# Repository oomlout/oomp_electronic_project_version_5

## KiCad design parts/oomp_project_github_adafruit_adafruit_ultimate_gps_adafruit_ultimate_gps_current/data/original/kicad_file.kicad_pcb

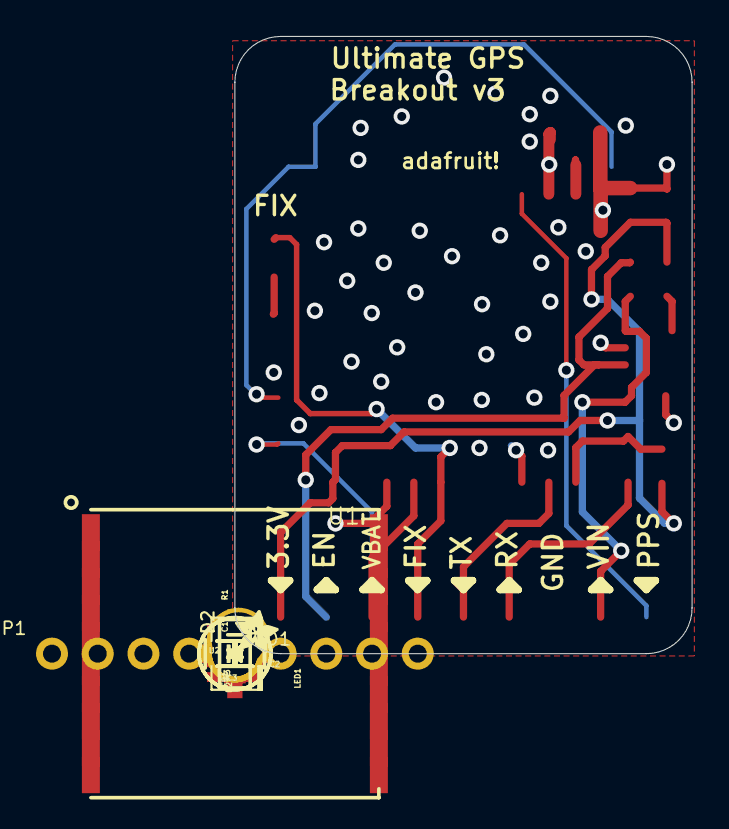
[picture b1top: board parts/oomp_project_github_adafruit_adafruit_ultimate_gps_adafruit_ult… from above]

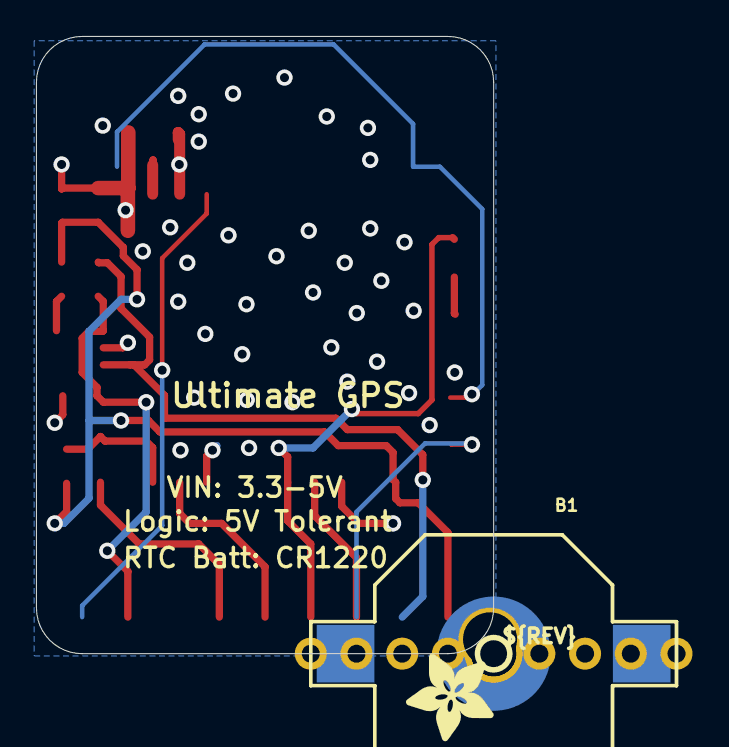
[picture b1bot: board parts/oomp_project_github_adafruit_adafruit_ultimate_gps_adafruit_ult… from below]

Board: 2 copper layers, 25.4 x 34.3 mm, 22 parts (3 on the bottom side), 14 nets.

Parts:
B1: CR1220
C1: 0.1uF; 0805-NO
C2, C3: 10uF; 0805-NO
D1: 1N4148; SOD-323
D2: CUS520; SOD-323
FB1: Ferrite; 0805-NO
FID1, FID2: FIDUCIAL""; FIDUCIAL_1MM
JP1: 1X09_ROUND_70
LED1: RED; CHIPLED_0805
R1: 1K; 0805-NO
R2, R3: 10K; 0805-NO
U1: FGPMMOPA6H
U2: MIC5225-3.3; SOT23-5
U$8, U$9: MOUNTINGHOLE2.5; MOUNTINGHOLE_2.5_PLATED
U$15: ADAFRUIT_2.5MM
U$16: PCBFEAT-REV-040
U$18: ADAFRUIT_5MM
U$20: U.FL

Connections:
1PPS: JP1.1, U1.P$13
3.3V: C1.1, C2.1, FB1.2, JP1.9, R3.1, U1.P$1
ENABLE: JP1.8, R2.1, U2.3
FIX: JP1.6, LED1.A, U1.P$5
GND: B1.-, C1.2, C2.2, C3.2, JP1.3, R1.1, U1.P$3, U1.P$8, U1.P$12, U1.P$19, U2.2, U$20.P$1, U$20.P$2
unnamed: B1.+$1, B1.+$2, D2.A
unnamed: LED1.C, R1.2
unnamed: FB1.1, U2.5
unnamed: U1.P$11, U$20.P$3
RX: D1.C, JP1.4
RX_3V: D1.A, R3.2, U1.P$10
TX: JP1.5, U1.P$9
VBACKUP: D2.C, JP1.7, U1.P$4
VIN: C3.1, JP1.2, R2.2, U2.1

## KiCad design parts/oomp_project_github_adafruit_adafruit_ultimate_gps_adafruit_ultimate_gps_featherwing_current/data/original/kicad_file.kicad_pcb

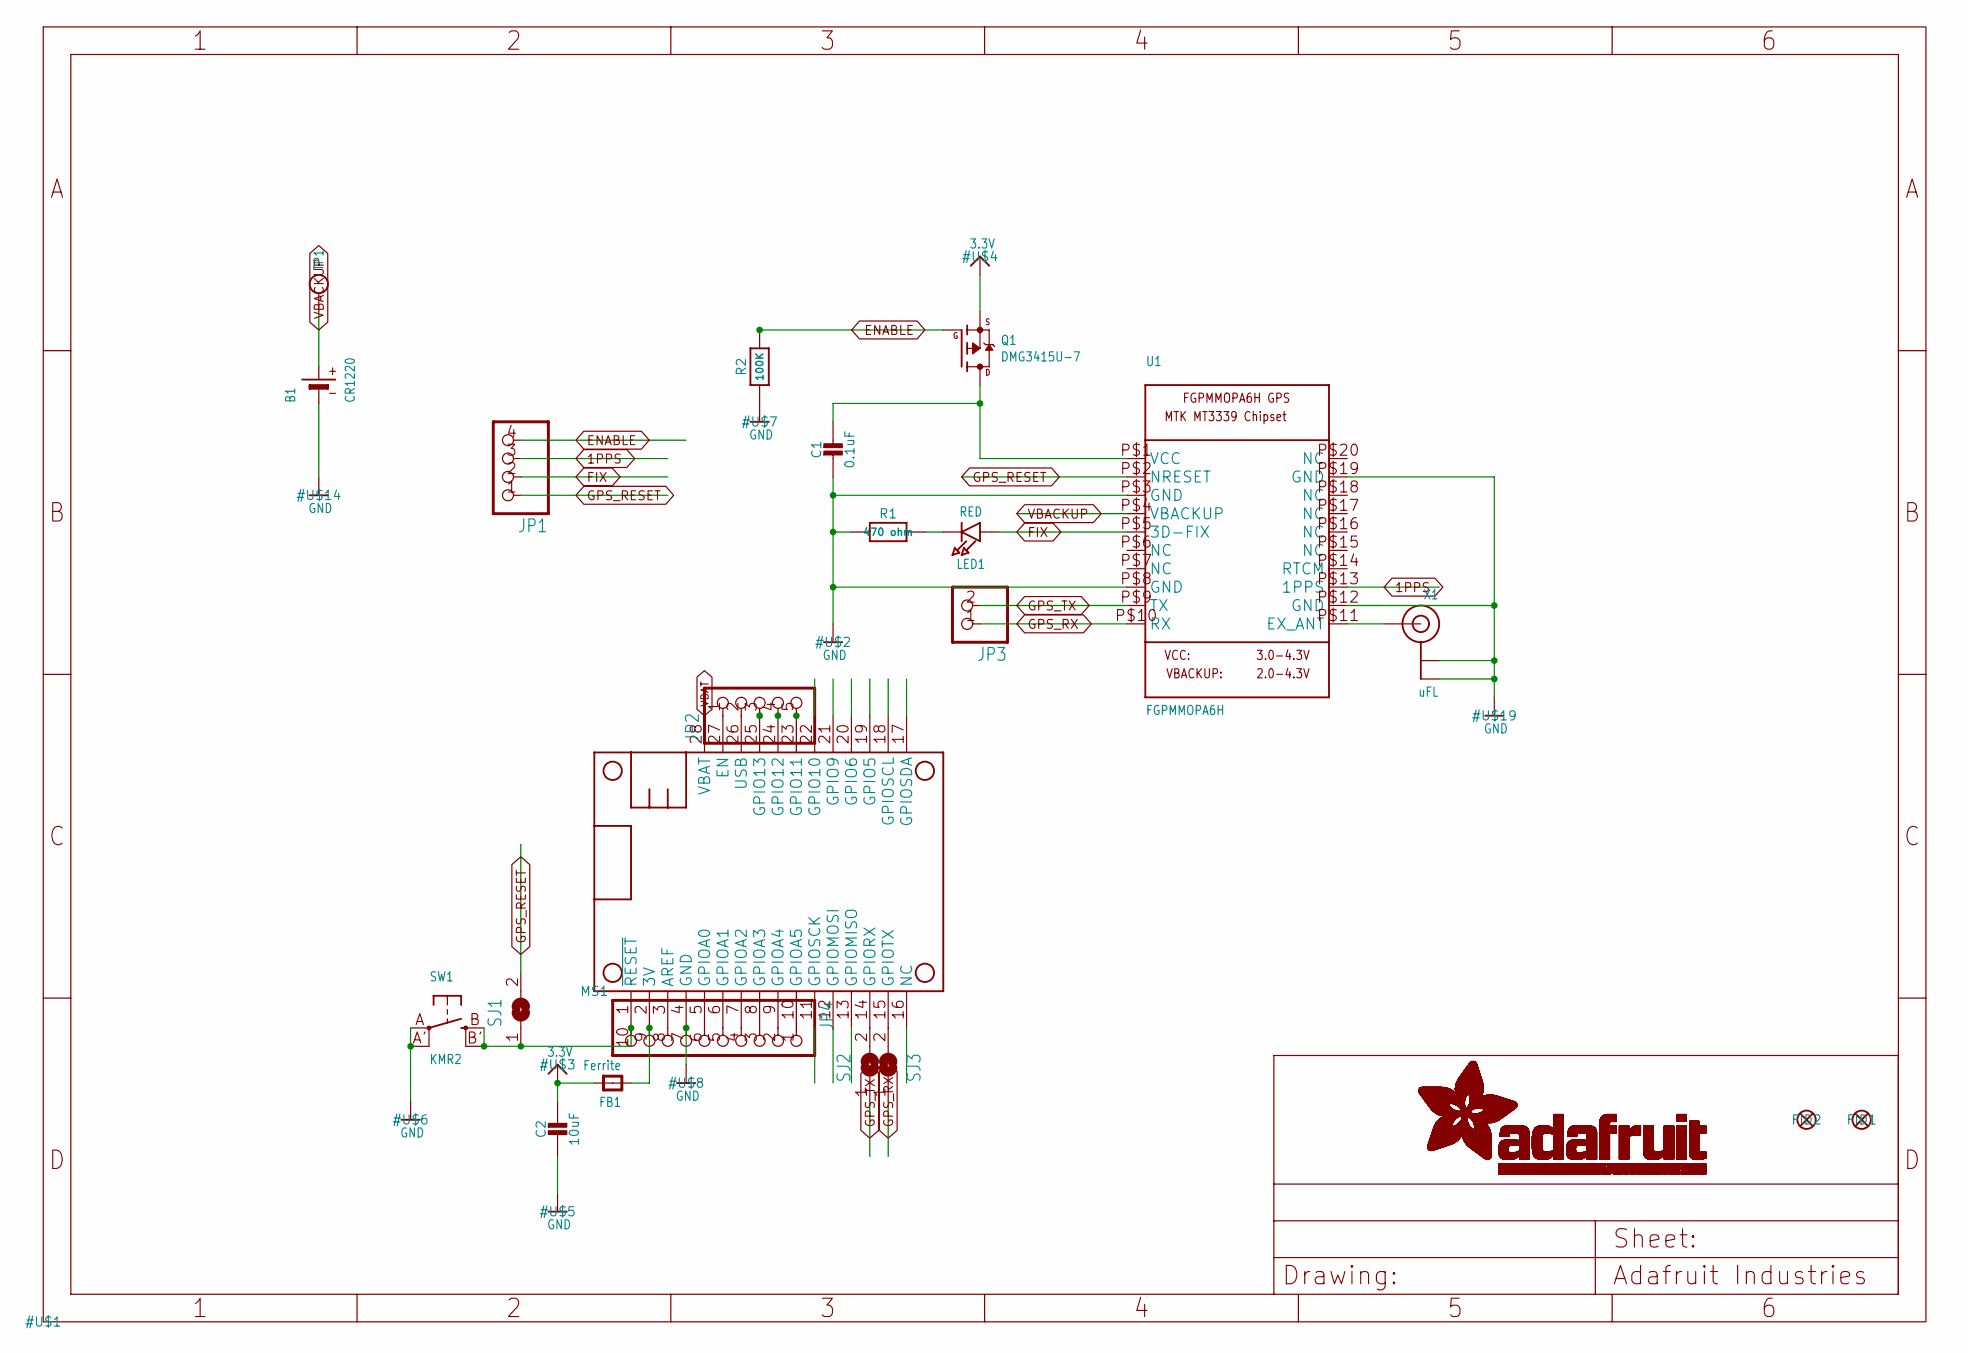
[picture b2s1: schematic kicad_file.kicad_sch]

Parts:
B1: CR1220; CR1220-2
C1: 0.1uF; 0805-NO
C2: 10uF; 0805-NO
FB1: Ferrite; 0805-NO
FID1, FID2: FIDUCIAL""; FIDUCIAL_1MM
JP1: HEADER-1X4ROUND; 1X04_ROUND
JP2: HEADER-1X570MIL; 1X05_ROUND_70
JP3: HEADER-1X2ROUND; 1X02_ROUND
JP4: HEADER-1X10ROUND; 1X10_ROUND
LED1: RED; CHIPLED_0805_NOOUTLINE
MS1: FEATHERWING
Q1: DMG3415U-7; SOT23-WIDE
R1: 470 ohm; 0805-NO
R2: 100K; 0805-NO
SJ1: SOLDERJUMPER; SOLDERJUMPER_ARROW_NOPASTE
SJ2, SJ3: SOLDERJUMPERCLOSED; SOLDERJUMPER_CLOSEDWIRE
SW1: KMR2; BTN_KMR2_4.6X2.8
TP1: TESTPOINTROUND1.5MM; TESTPOINT_ROUND_1.5MM
U1: FGPMMOPA6H
X1: uFL; U.FL

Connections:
1PPS: JP1.3, U1.P$13 (1PPS)
3.3V: C2.1, FB1.2, Q1.2 (S)
3V: FB1.1, JP4.9, MS1.2 (3V)
A: JP4.6, MS1.5 (GPIOA0)
AREF: JP4.8, MS1.3 (AREF)
B: JP4.5, MS1.6 (GPIOA1)
C: JP4.4, MS1.7 (GPIOA2)
D: JP4.3, MS1.8 (GPIOA3)
E: JP4.2, MS1.9 (GPIOA4)
EN: JP2.1, MS1.27 (EN)
ENABLE: JP1.4, Q1.1 (G), R2.2
F: JP4.1, MS1.10 (GPIOA5)
FIX: JP1.2, LED1.A, U1.P$5 (3D-FIX)
G: MS1.16 (NC)
GND: B1.-, C1.2, C2.2, JP4.7, MS1.4 (GND), R1.1, R2.1, SW1.A, SW1.A' (P1), U1.P$3 (GND), U1.P$8 (GND), U1.P$12 (GND), U1.P$19 (GND), X1.1 (GND), X1.2 (GND)
GPS_RESET: JP1.1, SJ1.2, U1.P$2 (NRESET)
GPS_RX: JP3.1, SJ3.1, U1.P$10 (RX)
GPS_TX: JP3.2, SJ2.1, U1.P$9 (TX)
H: MS1.19 (GPIO5)
I: MS1.20 (GPIO6)
J: MS1.21 (GPIO9)
K: MS1.22 (GPIO10)
L: JP2.5, MS1.23 (GPIO11)
M: JP2.4, MS1.24 (GPIO12)
MISO: MS1.13 (GPIOMISO)
MOSI: MS1.12 (GPIOMOSI)
N: JP2.3, MS1.25 (GPIO13)
unnamed: LED1.C, R1.2
unnamed: U1.P$11 (EX_ANT), X1.3 (SIGNAL)
unnamed: C1.1, Q1.3 (D), U1.P$1 (VCC)
RST: JP4.10, MS1.1 (~RESET), SJ1.1, SW1.B (S), SW1.B' (S1)
RX: MS1.14 (GPIORX), SJ2.2
SCK: MS1.11 (GPIOSCK)
SCL: MS1.18 (GPIOSCL)
SDA: MS1.17 (GPIOSDA)
TX: MS1.15 (GPIOTX), SJ3.2
USB: JP2.2, MS1.26 (USB)
VBACKUP: B1.+, TP1.P$1, U1.P$4 (VBACKUP)

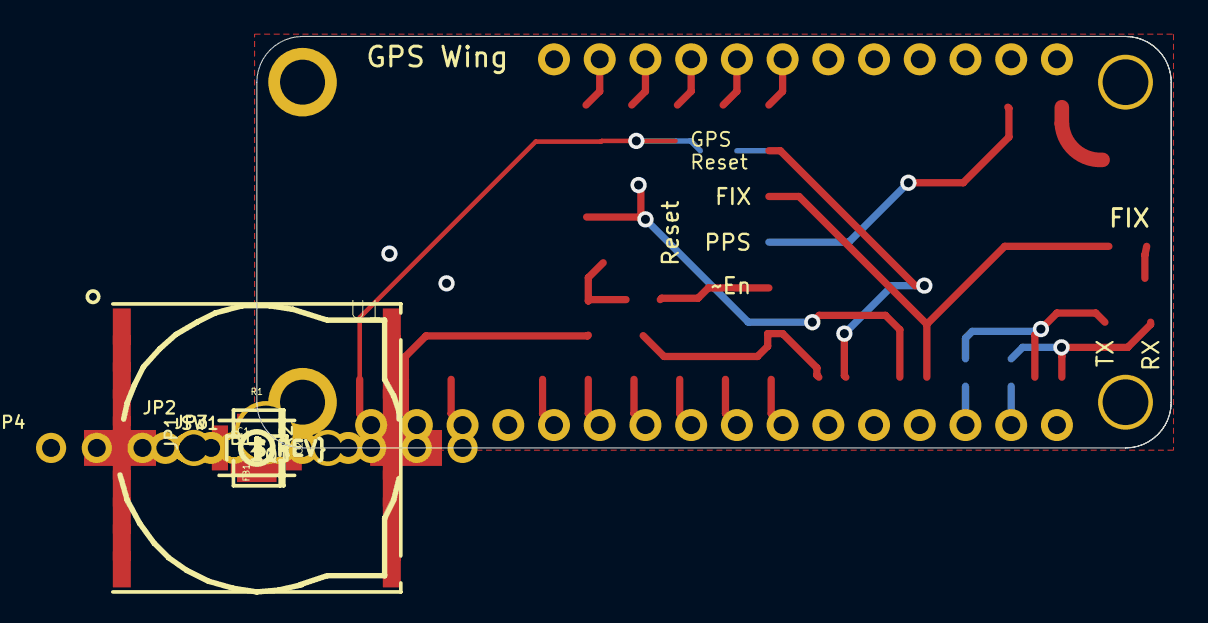
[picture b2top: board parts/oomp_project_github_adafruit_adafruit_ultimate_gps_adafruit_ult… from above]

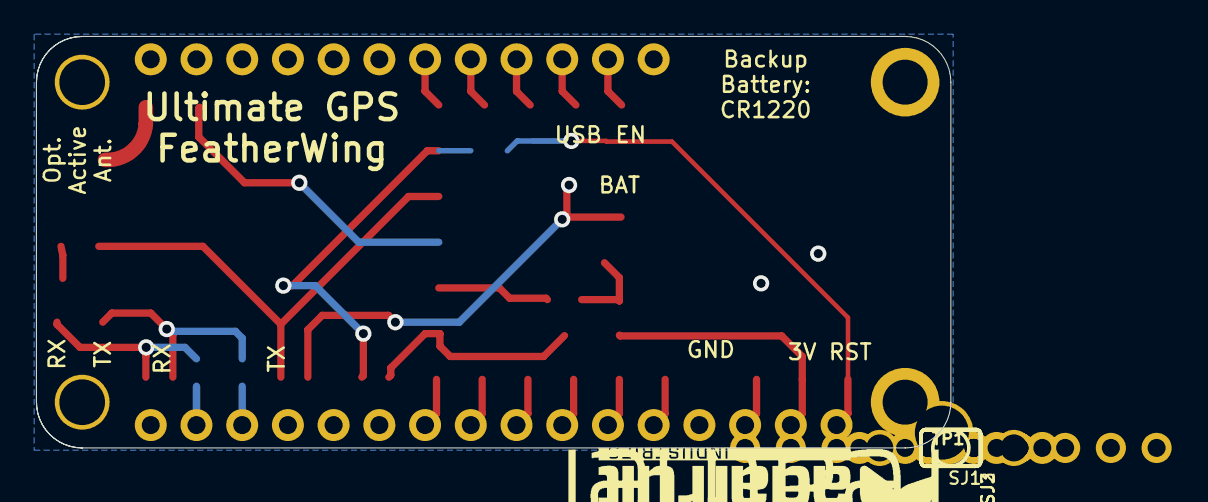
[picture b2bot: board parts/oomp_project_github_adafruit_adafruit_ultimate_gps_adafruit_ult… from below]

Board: 2 copper layers, 50.8 x 22.9 mm, 25 parts (6 on the bottom side), 28 nets.

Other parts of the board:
U$9: PCBFEAT-REV-040
U$10: FEATHERLOGO
U$11: ADAFRUIT_TEXT_20MM

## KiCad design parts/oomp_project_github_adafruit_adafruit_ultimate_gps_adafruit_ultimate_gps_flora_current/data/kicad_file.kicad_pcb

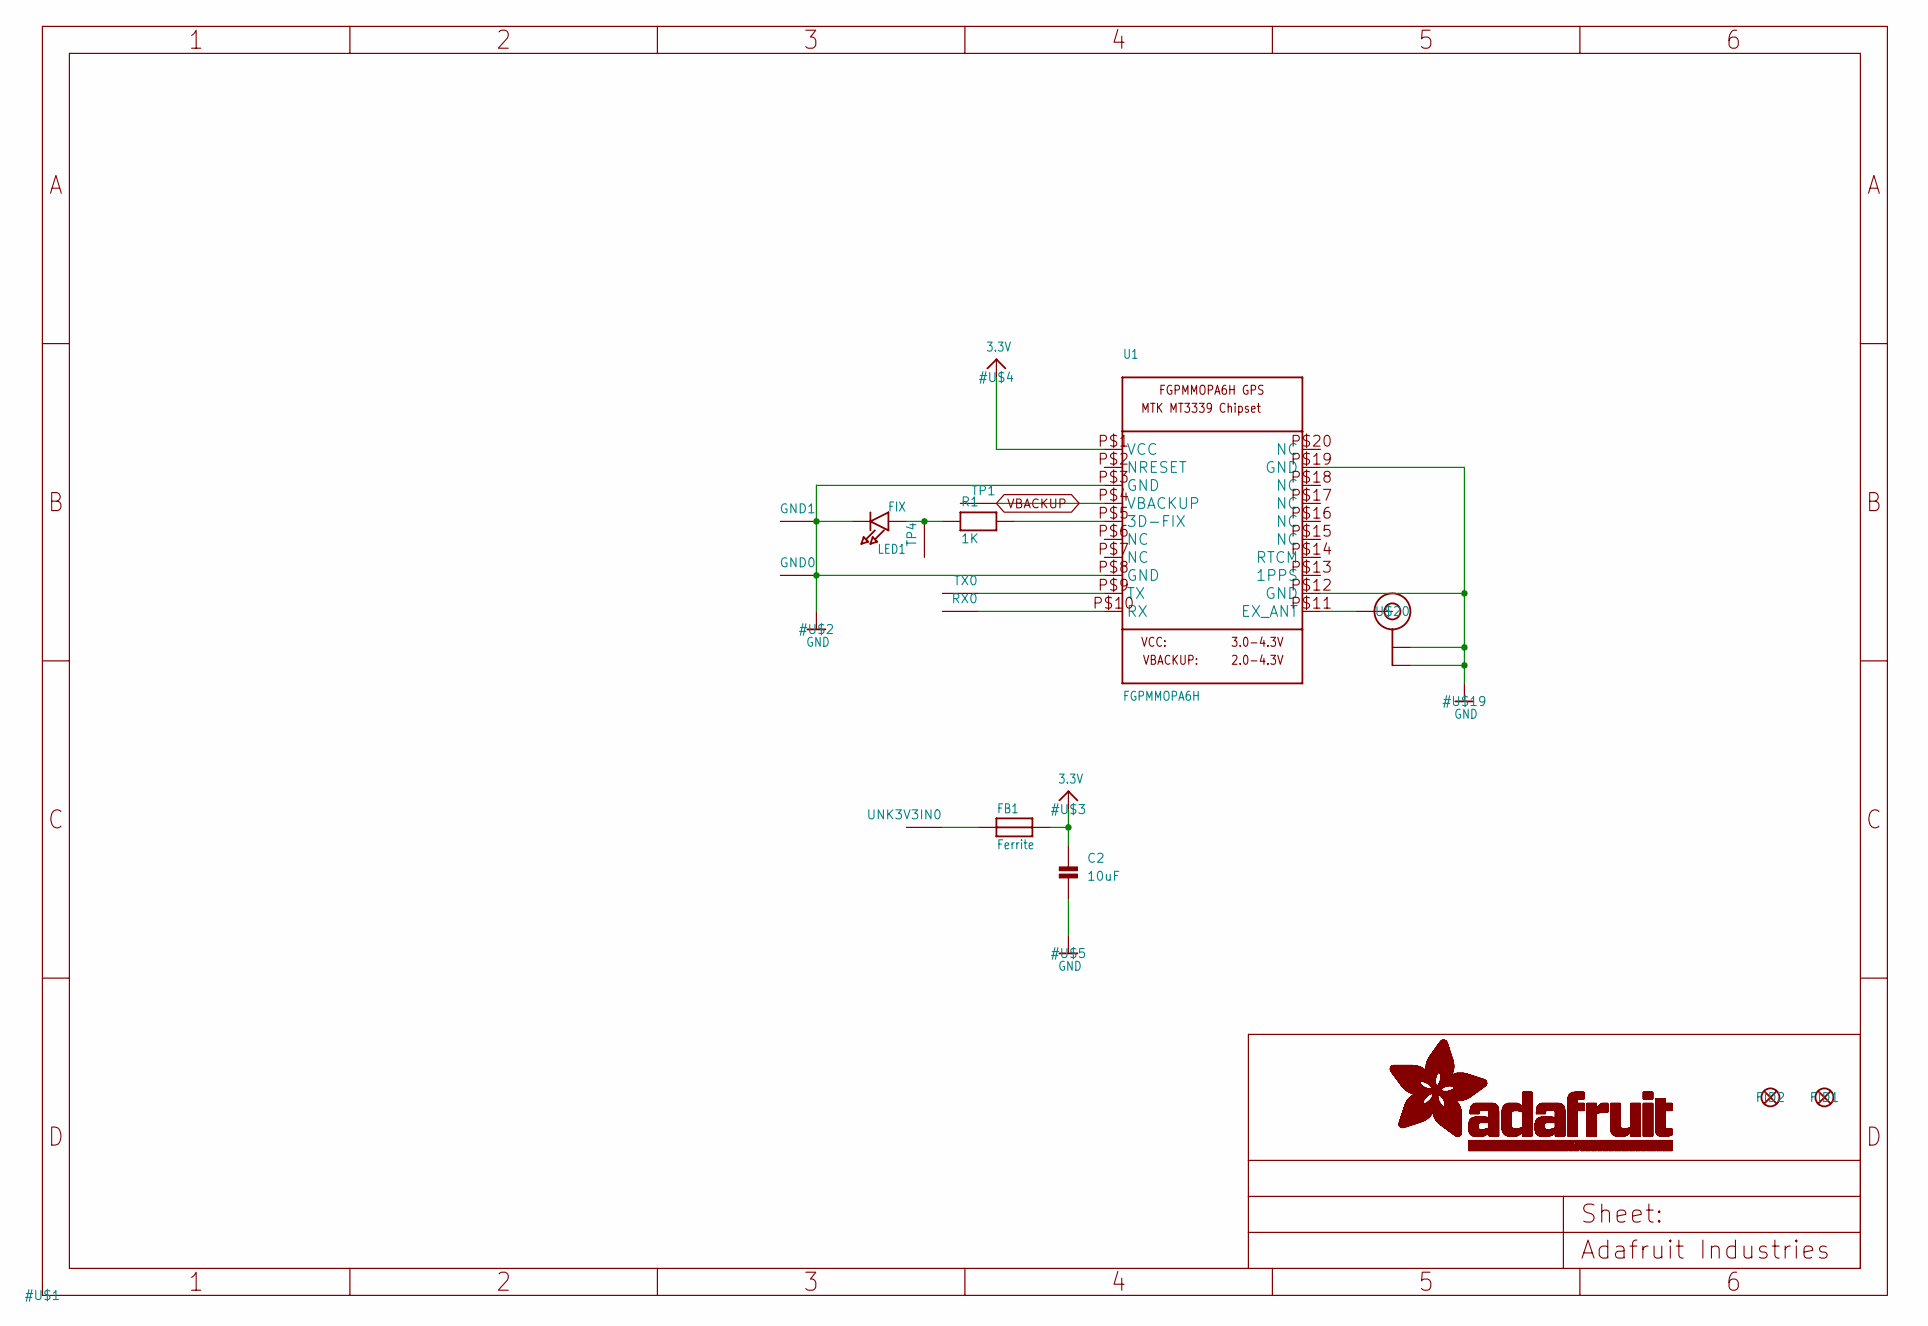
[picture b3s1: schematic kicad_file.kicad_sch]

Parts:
C2: 10uF; 0805
FB1: Ferrite; 0805
FID1, FID2: FIDUCIAL""; FIDUCIAL_1MM
GND0, GND1: SEWTAP-2.0IN; SEWINGTAP_2.0
LED1: FIX; CHIPLED_0805
R1: 1K; 0805
RX0: SEWTAP-2.0IN; SEWINGTAP_2.0
TP1, TP4: SEWTAP-2.0IN; SEWINGTAP_2.0
TX0: SEWTAP-2.0IN; SEWINGTAP_2.0
U1: FGPMMOPA6H
U$20: U.FL
UNK3V3IN0: SEWTAP-2.0IN; SEWINGTAP_2.0

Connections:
3.3V: C2.1, FB1.2, U1.P$1 (VCC)
GND: C2.2, GND0.P$1, GND1.P$1, LED1.C, U1.P$3 (GND), U1.P$8 (GND), U1.P$12 (GND), U1.P$19 (GND), U$20.P$1 (GND), U$20.P$2 (GND)
unnamed: LED1.A, R1.1, TP4.P$1
unnamed: R1.2, U1.P$5 (3D-FIX)
unnamed: FB1.1, UNK3V3IN0.P$1
unnamed: U1.P$11 (EX_ANT), U$20.P$3 (SIGNAL)
RX: RX0.P$1, U1.P$10 (RX)
TX: TX0.P$1, U1.P$9 (TX)
VBACKUP: TP1.P$1, U1.P$4 (VBACKUP)

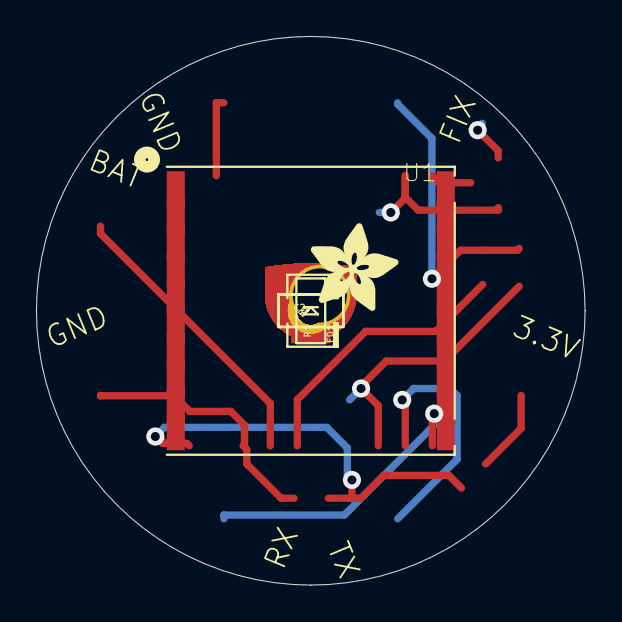
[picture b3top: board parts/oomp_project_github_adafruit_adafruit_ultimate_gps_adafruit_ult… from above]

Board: 2 copper layers, 30.5 x 30.5 mm, 17 parts (1 on the bottom side), 9 nets.

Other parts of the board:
U$6: ADAFRUIT_5MM
U$7: FLORASMALL

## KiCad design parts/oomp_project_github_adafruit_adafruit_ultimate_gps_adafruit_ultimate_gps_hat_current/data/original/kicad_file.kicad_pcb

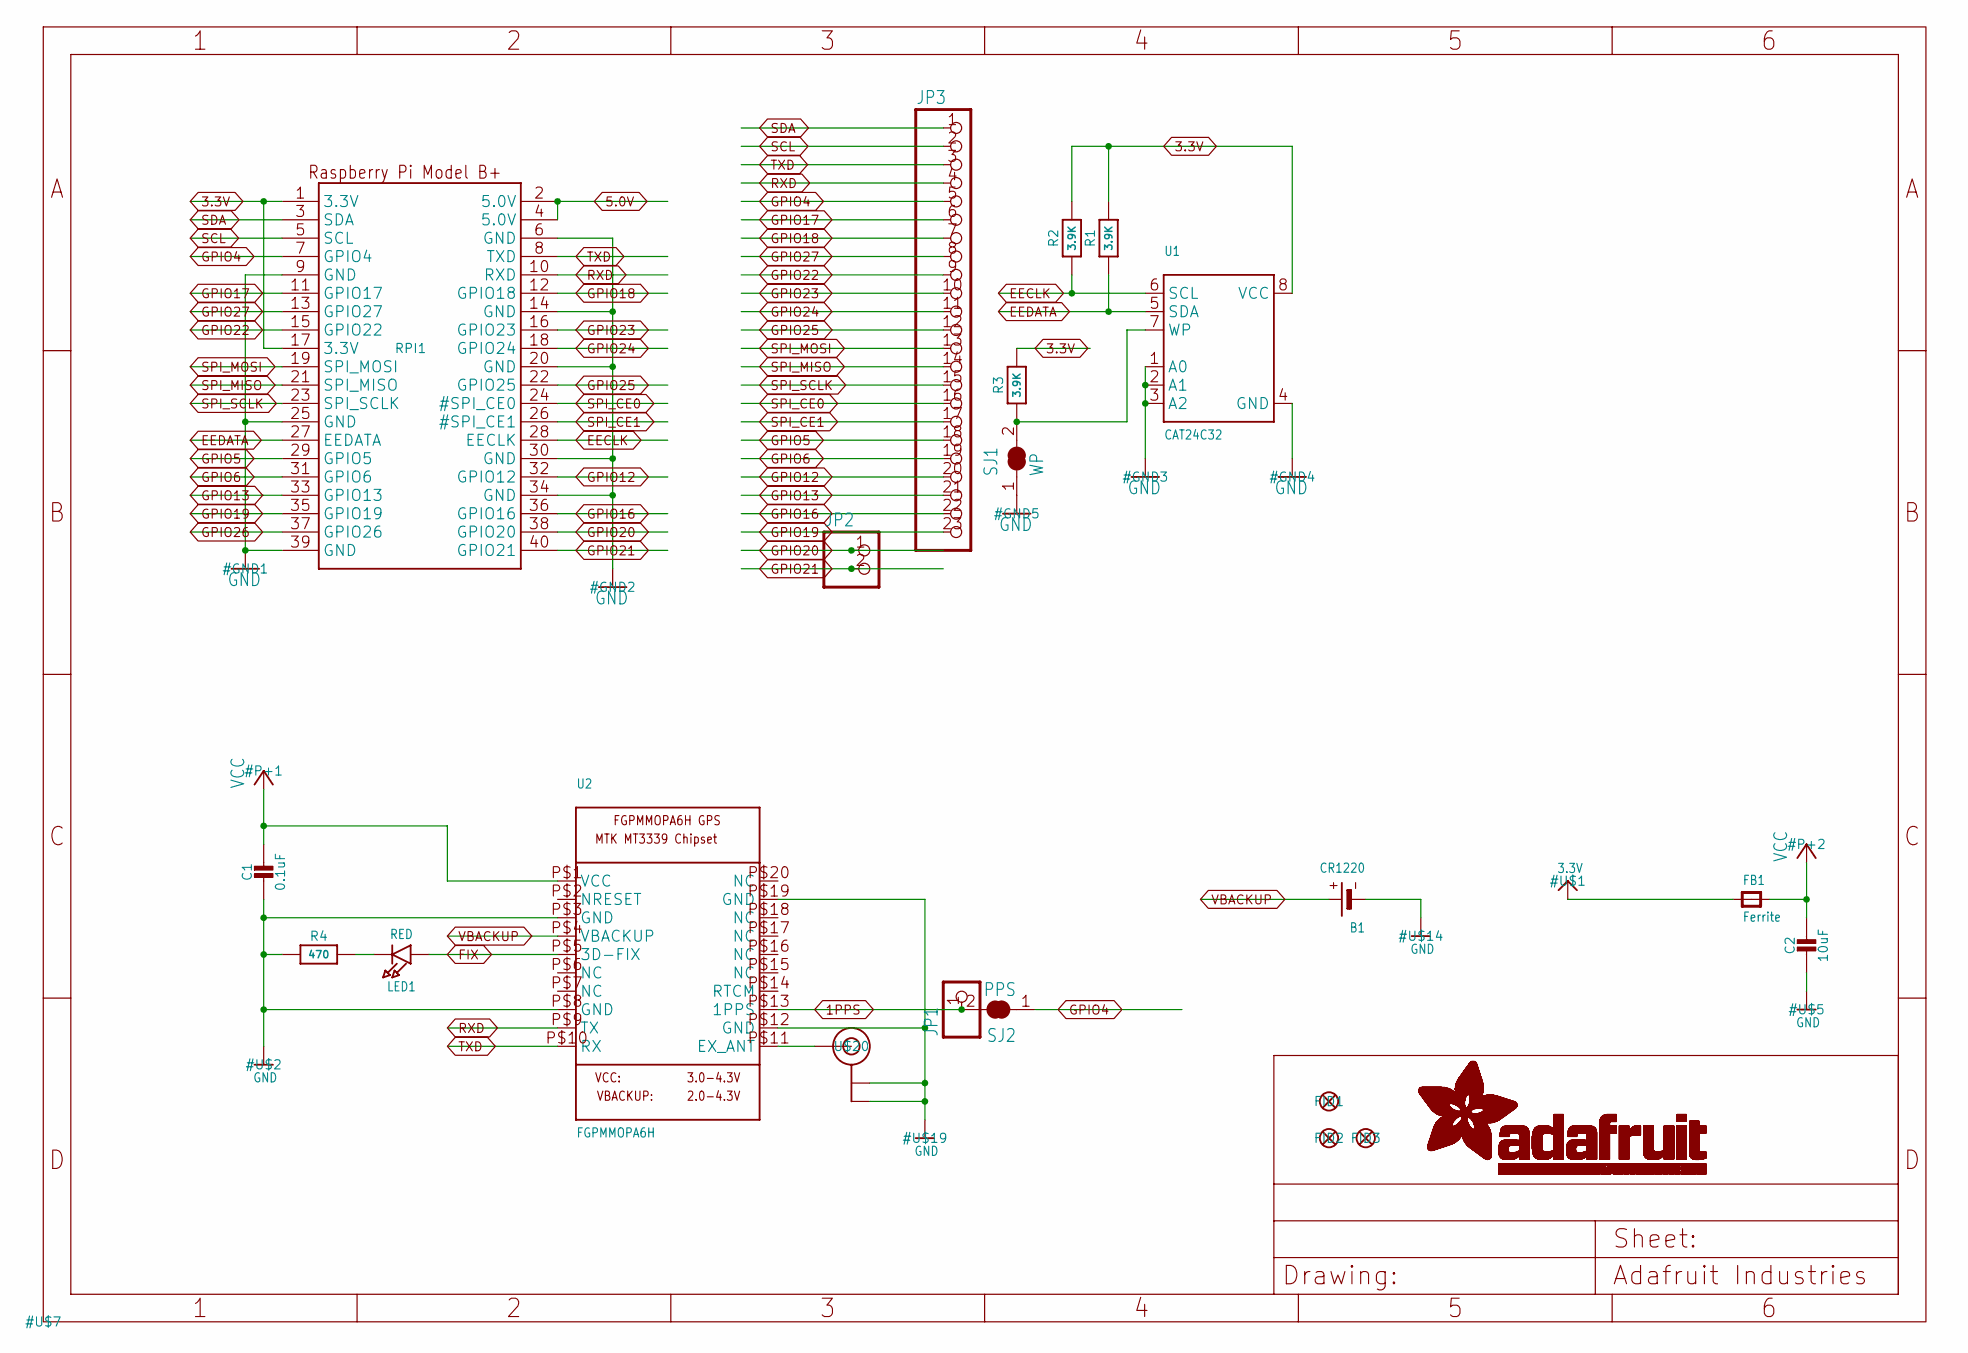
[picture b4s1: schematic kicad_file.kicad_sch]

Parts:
B1: CR1220
C1: 0.1uF; 0805-NO
C2: 10uF; 0805-NO
FB1: Ferrite; 0805
FID1, FID2, FID3: FIDUCIAL_1MM
JP1: PINHD-1X1CB; 1X01-CLEANBIG
JP2: HEADER-1X2ROUND; 1X02_ROUND
JP3: HEADER-1X23; 1X23_ROUND_70MIL
LED1: RED; CHIPLED_0805
R1, R2, R3: 3.9K; 0805-NO
R4: 470; 0805-NO
RPI1: RASPBERRYPI_BPLUS_HATSLOTS; PI_HAT_SLOTS
SJ1: WP; SOLDERJUMPER_CLOSEDWIRE
SJ2: PPS; SOLDERJUMPER_CLOSEDWIRE
U1: CAT24C32; SOIC8_150MIL
U2: FGPMMOPA6H
U$20: U.FL

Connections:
1PPS: JP1.1, SJ2.2, U2.P$13 (1PPS)
3.3V: FB1.1, R1.2, R2.2, R3.2, RPI1.1 (3.3V), RPI1.17 (3.3V), U1.8 (VCC)
5.0V: RPI1.2 (5.0V), RPI1.4 (5.0V)
EECLK: R2.1, RPI1.28 (EECLK), U1.6 (SCL)
EEDATA: R1.1, RPI1.27 (EEDATA), U1.5 (SDA)
FIX: LED1.A, U2.P$5 (3D-FIX)
GND: B1.-, C1.2, C2.2, R4.1, RPI1.6 (GND), RPI1.9 (GND), RPI1.14 (GND), RPI1.20 (GND), RPI1.25 (GND), RPI1.30 (GND), RPI1.34 (GND), RPI1.39 (GND), SJ1.1, U1.1 (A0), U1.2 (A1), U1.3 (A2), U1.4 (GND), U2.P$3 (GND), U2.P$8 (GND), U2.P$12 (GND), U2.P$19 (GND), U$20.P$1 (GND), U$20.P$2 (GND)
GPIO4: JP3.5, RPI1.7 (GPIO4), SJ2.1
GPIO5: JP3.18, RPI1.29 (GPIO5)
GPIO6: JP3.19, RPI1.31 (GPIO6)
GPIO12: JP3.20, RPI1.32 (GPIO12)
GPIO13: JP3.21, RPI1.33 (GPIO13)
GPIO16: JP3.22, RPI1.36 (GPIO16)
GPIO17: JP3.6, RPI1.11 (GPIO17)
GPIO18: JP3.7, RPI1.12 (GPIO18)
GPIO19: JP3.23, RPI1.35 (GPIO19)
GPIO20: JP2.1, RPI1.38 (GPIO20)
GPIO21: JP2.2, RPI1.40 (GPIO21)
GPIO22: JP3.9, RPI1.15 (GPIO22)
GPIO23: JP3.10, RPI1.16 (GPIO23)
GPIO24: JP3.11, RPI1.18 (GPIO24)
GPIO25: JP3.12, RPI1.22 (GPIO25)
GPIO26: RPI1.37 (GPIO26)
GPIO27: JP3.8, RPI1.13 (GPIO27)
unnamed: R3.1, SJ1.2, U1.7 (WP)
unnamed: LED1.C, R4.2
unnamed: U2.P$11 (EX_ANT), U$20.P$3 (SIGNAL)
RXD: JP3.4, RPI1.10 (RXD), U2.P$9 (TX)
SCL: JP3.2, RPI1.5 (SCL)
SDA: JP3.1, RPI1.3 (SDA)
SPI_CE0: JP3.16, RPI1.24 (#SPI_CE0)
SPI_CE1: JP3.17, RPI1.26 (#SPI_CE1)
SPI_MISO: JP3.14, RPI1.21 (SPI_MISO)
SPI_MOSI: JP3.13, RPI1.19 (SPI_MOSI)
SPI_SCLK: JP3.15, RPI1.23 (SPI_SCLK)
TXD: JP3.3, RPI1.8 (TXD), U2.P$10 (RX)
VBACKUP: B1.+$1 (+), B1.+$2 (+), U2.P$4 (VBACKUP)
VCC: C1.1, C2.1, FB1.2, U2.P$1 (VCC)

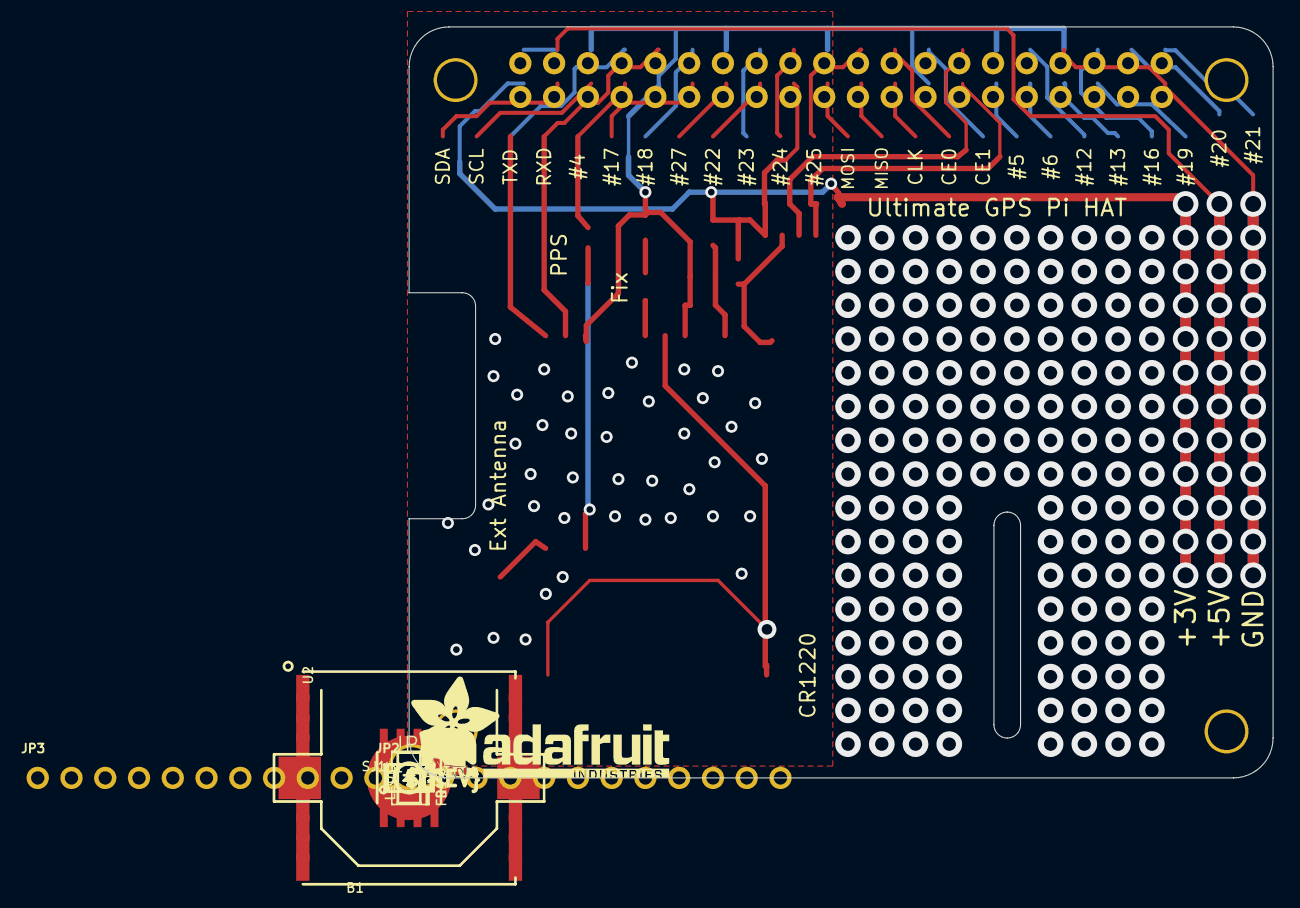
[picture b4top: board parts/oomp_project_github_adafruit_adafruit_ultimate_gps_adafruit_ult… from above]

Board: 2 copper layers, 65.0 x 56.5 mm, 24 parts (0 on the bottom side), 37 nets.

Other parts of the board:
U$3: ADAFRUIT_TEXT_20MM
U$4: PIHATLOGO
U$6: PCBFEAT-REV-056

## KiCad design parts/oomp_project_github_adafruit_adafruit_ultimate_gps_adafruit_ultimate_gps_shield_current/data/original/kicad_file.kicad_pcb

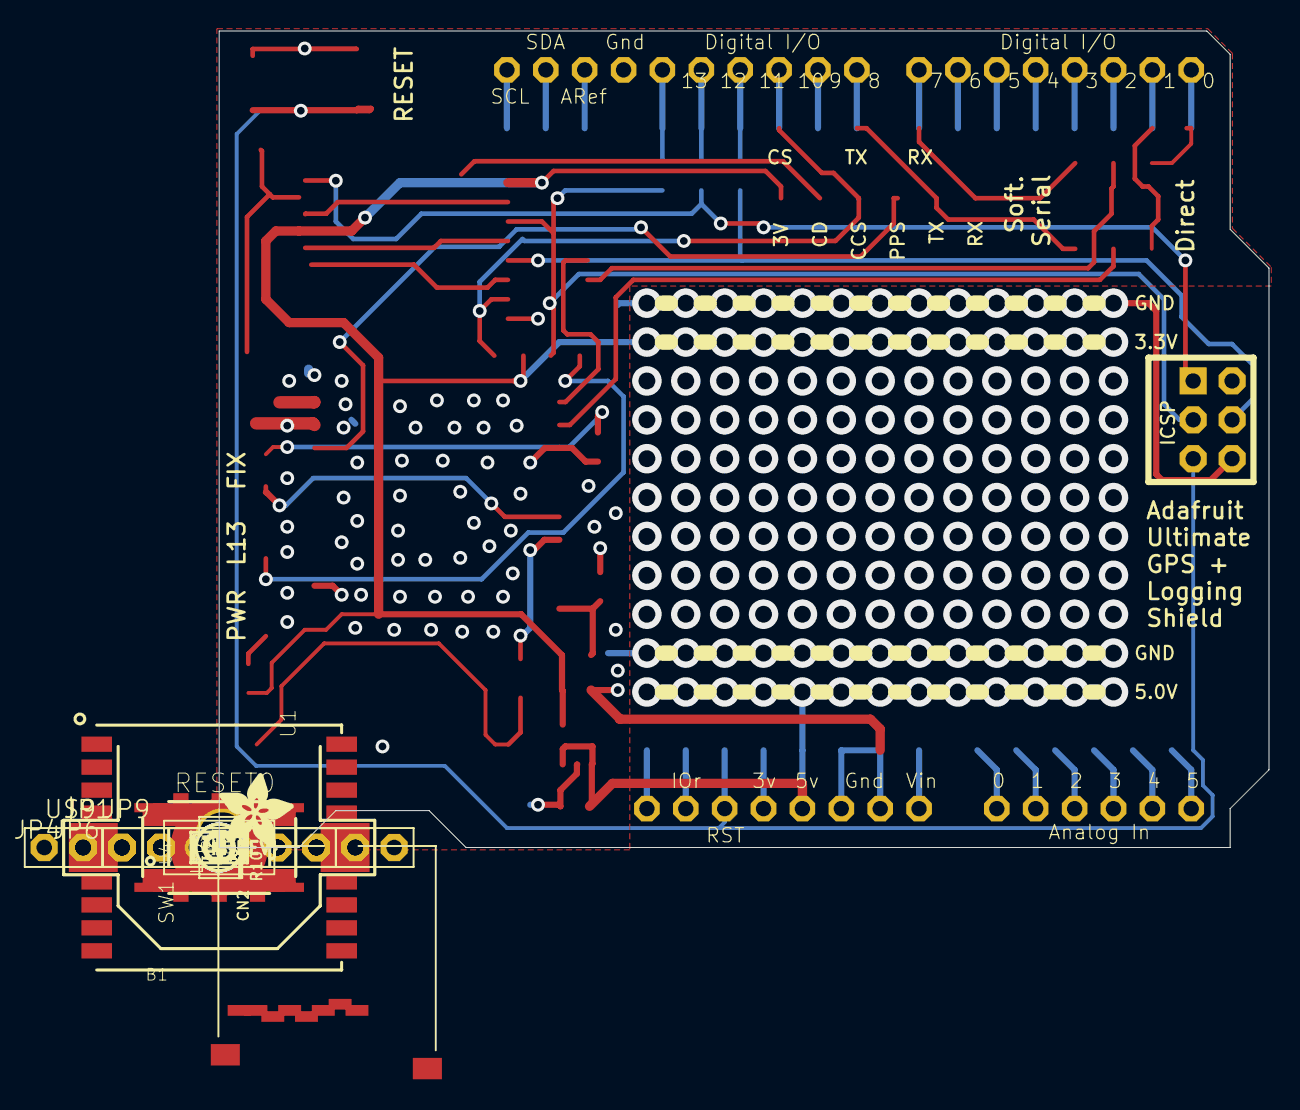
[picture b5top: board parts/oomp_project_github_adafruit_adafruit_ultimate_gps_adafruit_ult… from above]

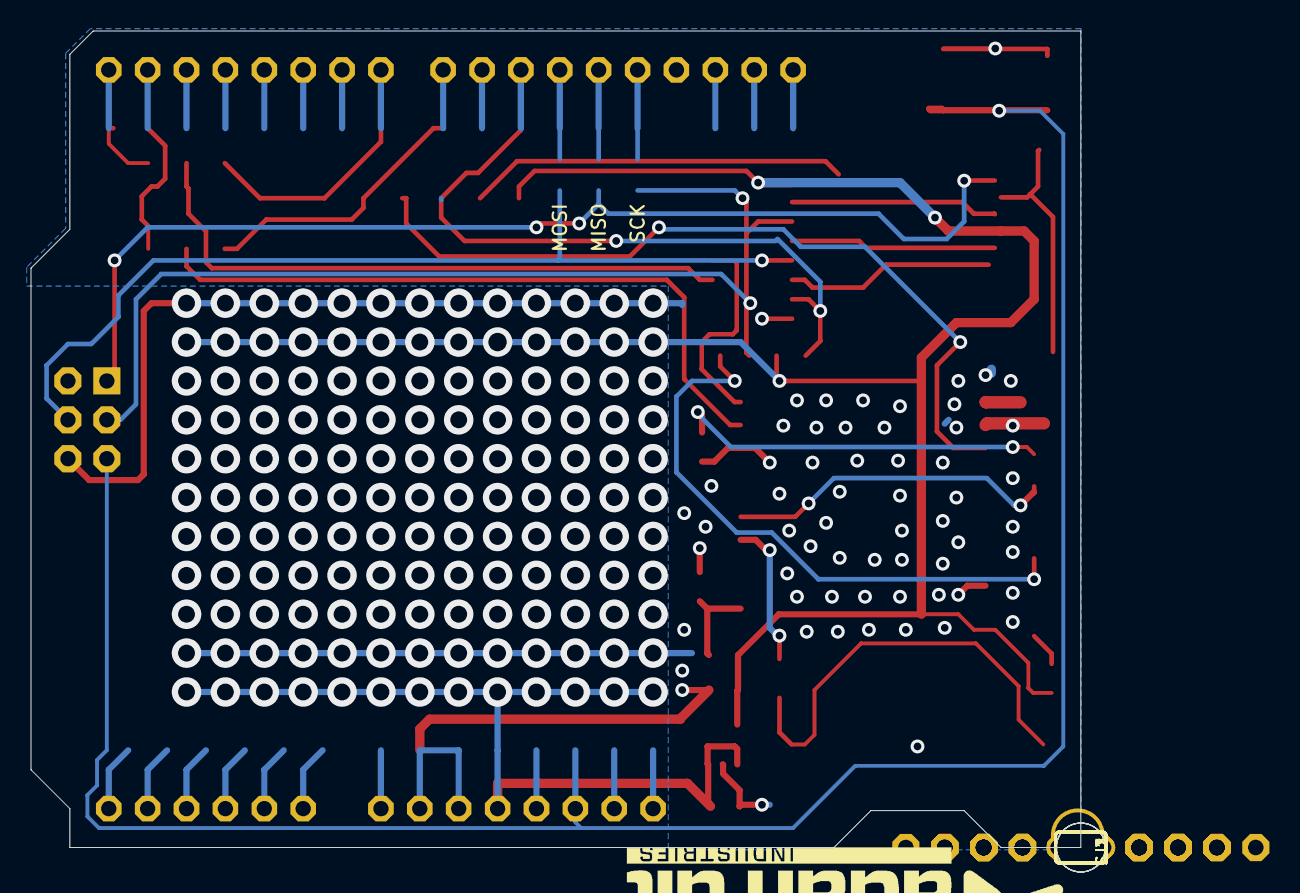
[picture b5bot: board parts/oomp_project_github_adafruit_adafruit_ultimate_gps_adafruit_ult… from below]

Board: 2 copper layers, 68.6 x 53.3 mm, 37 parts (4 on the bottom side), 50 nets.

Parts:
B1: CR1220
C1: 1uF; 0805-NO
C2, C3: 10uF; 0805-NO
CN2: MICROSD
D1: 1n4148; SOD-323
FB1: Ferrite; 0805
FID1, FID2: FIDUCIAL""; FIDUCIAL_1MM
JP1: D0-D7; 1X08-BIG
JP4: 1X08-BIG
JP6, JP9: 1X06-BIG
LED1: red; CHIPLED_0805_NOOUTLINE
LED4: yellow; CHIPLED_0805_NOOUTLINE
LED5: green; CHIPLED_0805_NOOUTLINE
M1: ARDUINO_R3_ICSP_NODIM; ARDUINOR3_ICSP_NODIM
R1: 1K; 0805-NO
R5: 10K; 0805-NO
R9, R10: 1k; 0805-NO
RESET0: Reset; EVQ-Q2
SJ1, SJ2, SJ3: SOLDERJUMPER_ARROW_NOPASTE
SW1: EG1390
U1: FGPMMOPA6H
U2: MIC5225-3.3; SOT23-5
U4: 4050; SOIC16
U$9: 1X10-BIG
U$13: ADAFRUIT_5MM
U$15: ADAFRUIT_TEXT_30MM
U$16: PCBFEAT-REV-040
U$20: U.FL
UNK_HOLE_0: dummyfp0
UNK_HOLE_1: dummyfp1
UNK_HOLE_2: dummyfp2

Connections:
1PPS: JP6.3, U1.P$13
3.3V: C2.1, CN2.4, FB1.1, JP6.6, R5.1, R10.2, U2.5, U4.1
3V: JP1.4, M1.3V
+5V: C3.1, JP1.5, M1.5V, U2.1, U2.3
A0: JP9.1, M1.A0
A1: JP9.2, M1.A1
A2: JP9.3, M1.A2
A3: JP9.4, M1.A3
A4: JP9.5, M1.A4
A5: JP9.6, M1.A5
AREF: M1.AREF, U$9.3
D0: JP4.1, M1.D0, SW1.O2
D1: JP4.2, M1.D1, SW1.O1
D2: JP4.3, M1.D2
D3: JP4.4, M1.D3
D4: JP4.5, M1.D4
D5: JP4.6, M1.D5
D6: JP4.7, M1.D6
D7: JP4.8, JP6.1, M1.D7, SW1.S2
D8: JP6.2, M1.D8, SW1.S1, U$9.10
D9: M1.D9, U$9.9
D11: M1.D11, SJ3.2, U$9.7
D12: M1.D12, SJ2.2, U$9.6
D13: M1.D13, SJ1.2, U$9.5
FIX: LED1.A, U1.P$5
GND: B1.-, C1.2, C2.2, C3.2, CN2.6, CN2.MT1, CN2.MT2, JP1.6, JP1.7, LED4.C, LED5.C, M1.GND, M1.GND@1, M1.GND@2, M1.GND@3, R1.1, RESET0.B, RESET0.B', U1.P$3, U1.P$8, U1.P$12, U1.P$19, U2.2, U4.8, U$9.4, U$20.P$1, U$20.P$2
IOREF: JP1.2, M1.IOREF
MISO: CN2.7, M1.MISO, SJ2.1
MOSI: M1.MOSI, SJ3.1, U4.5
unnamed: C1.1, FB1.2, U1.P$1
unnamed: LED1.C, R1.2
unnamed: B1.+$1, B1.+$2, D1.A
unnamed: U1.P$11, U$20.P$3
unnamed: LED4.A, R9.1
unnamed: LED5.A, R10.1
NC: JP1.1, M1.RESERVED
RESET: JP1.3, M1.RESET, M1.RESET_ICSP, RESET0.A, RESET0.A'
RX: U1.P$10, U4.12
RX_5V: SW1.P2, U4.11
SCK: M1.SCK, R9.2, SJ1.1, U4.3
SCL: M1.SCL, U$9.1
SDA: M1.SDA, U$9.2
SD_CD: CN2.CD1, JP6.5
SD_CS: JP6.4, M1.D10, R5.2, U4.7, U$9.8
SD_CSIN: CN2.2, U4.6
SD_DATAIN: CN2.3, U4.4
SD_SCKIN: CN2.5, U4.2
TX: SW1.P1, U1.P$9
VBACKUP: D1.C, U1.P$4
VIN: JP1.8, M1.VIN
